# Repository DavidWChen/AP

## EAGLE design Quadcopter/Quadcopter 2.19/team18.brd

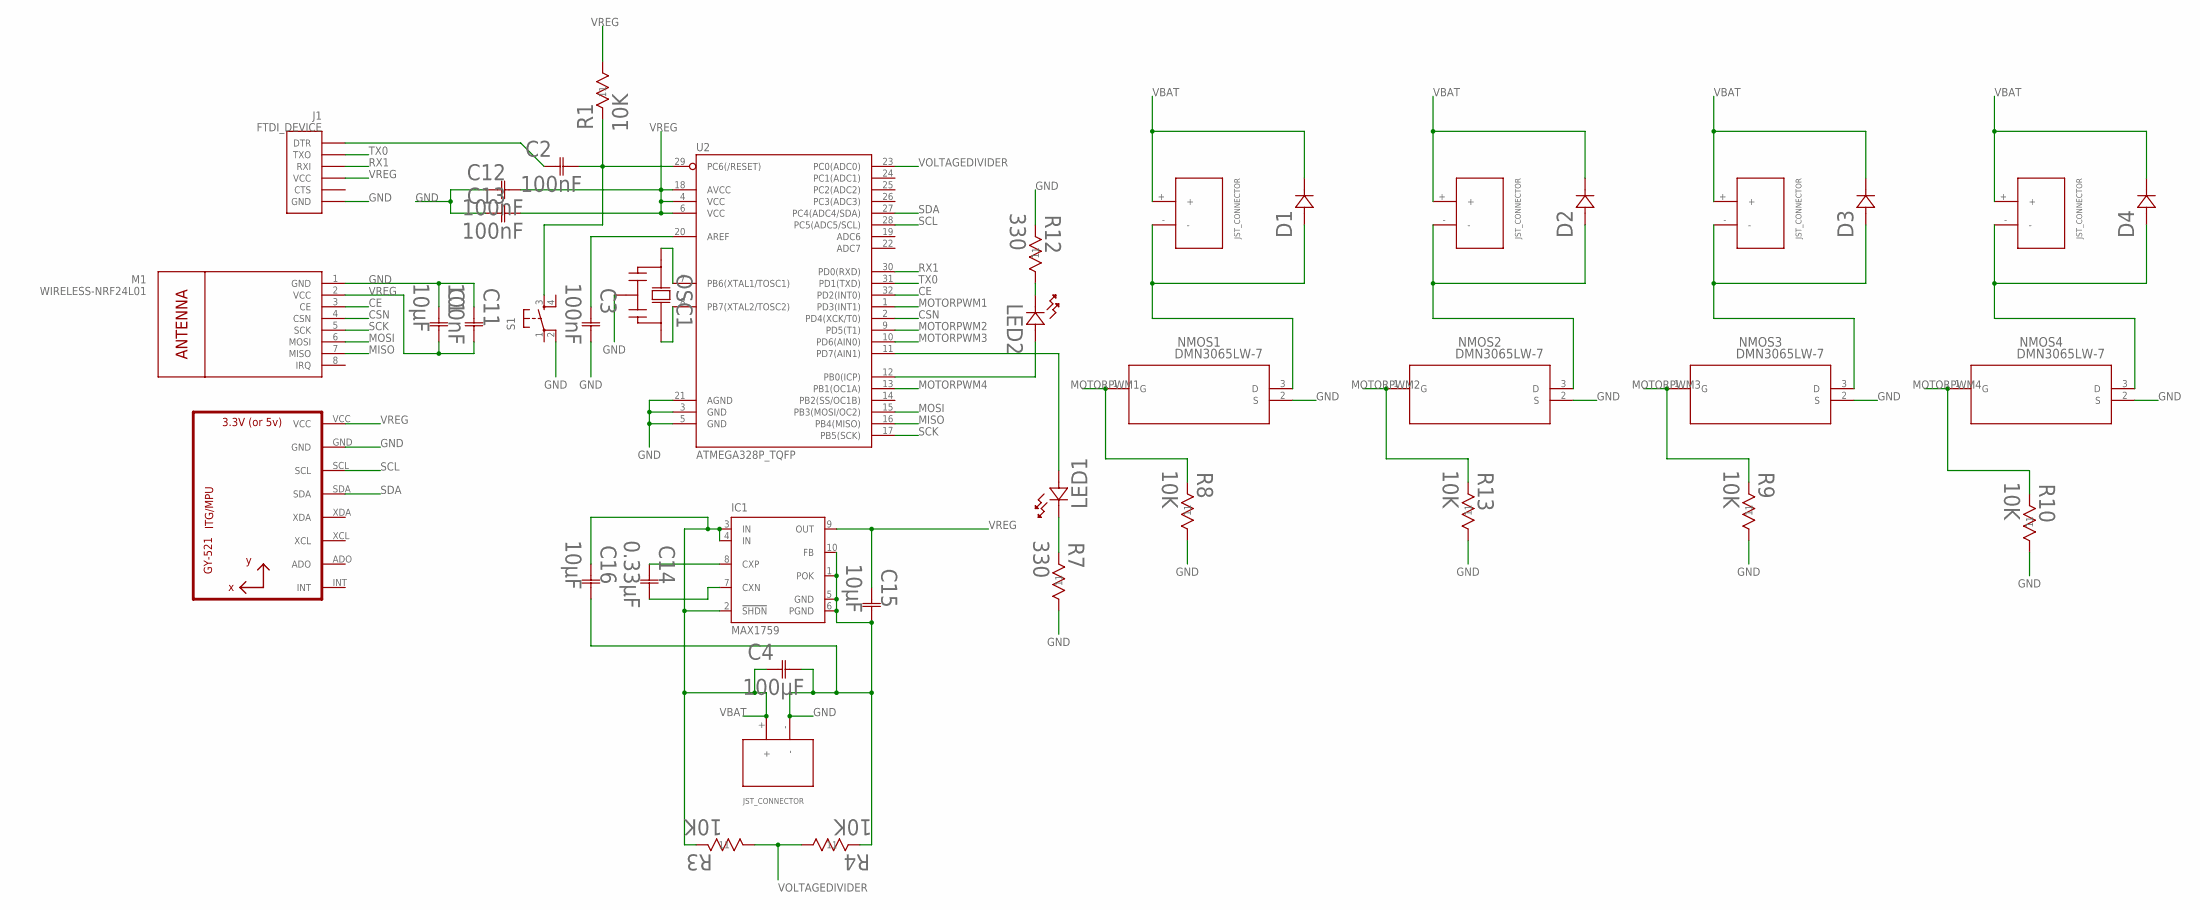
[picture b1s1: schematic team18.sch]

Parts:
BATTERY: JST_CONNECTOR_FEMALE
C1, C15, C16: 10µF; G-188
C2, C3, C11, C12, C13: 100nF; CAP_1608
C4: 100µF; CAP_3216
C14: 0.33µF; G-188
D1, D2, D3, D4: BAT60JFILM; SOD-323
IC1: MAX1759; UMAX10
J1: FTDI_DEVICE; FTDI_DEVICE_SIDE
LED1, LED2: 5988070107F; LED_DIALIGHT_598
M1: WIRELESS-NRF24L01
MOTOR1, MOTOR2, MOTOR3, MOTOR4: JST_CONNECTOR_FEMALE
NMOS1, NMOS2, NMOS3, NMOS4: DMN3065LW-7; SOT-323W/NEW
OSC1: CSTCE8M00G52-R0; CSTCE
R1, R3, R4, R8, R9, R10, R13: 10K; 0603
R7, R12: 330; BO_CR0603
S1: TAC_SWITCHSMD; TACTILE_SWITCH_SMD
U1: GY-521MPU6050; GY-521
U2: ATMEGA328P_TQFP; TQFP32-08

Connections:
CE: M1.3 (CE), U2.32 (PD2(INT0))
CSN: M1.4 (CSN), U2.2 (PD4(XCK/T0))
GND: BATTERY.-, C1.1 (11), C3.2 (22), C4.2 (22), C11.1 (11), C12.1 (11), C13.1 (11), C15.2 (22), C16.2 (22), IC1.1 (POK), IC1.5 (GND), IC1.6 (PGND), IC1.10 (FB), J1.P$6 (GND), M1.1 (GND), NMOS1.2 (S), NMOS2.2 (S), NMOS3.2 (S), NMOS4.2 (S), OSC1.2 (22), R4.1 (11), R7.2 (22), R8.2 (22), R9.2 (22), R10.2 (22), R12.1 (11), R13.2 (22), S1.2, U1.GND, U2.3 (GND), U2.5 (GND), U2.21 (AGND)
MISO: M1.7 (MISO), U2.16 (PB4(MISO))
MOSI: M1.6 (MOSI), U2.15 (PB3(MOSI/OC2))
MOTORPWM1: NMOS1.1 (G), R8.1 (11), U2.1 (PD3(INT1))
MOTORPWM2: NMOS2.1 (G), R13.1 (11), U2.9 (PD5(T1))
MOTORPWM3: NMOS3.1 (G), R9.1 (11), U2.10 (PD6(AIN0))
MOTORPWM4: NMOS4.1 (G), R10.1 (11), U2.13 (PB1(OC1A))
unnamed: D2.2 (22), MOTOR2.-, NMOS2.3 (D)
unnamed: C14.1 (11), IC1.8 (CXP)
unnamed: D3.2 (22), MOTOR3.-, NMOS3.3 (D)
unnamed: D4.2 (22), MOTOR4.-, NMOS4.3 (D)
unnamed: C2.2 (22), R1.1 (11), S1.3, U2.29 (PC6(/RESET))
unnamed: D1.2 (22), MOTOR1.-, NMOS1.3 (D)
unnamed: C2.1 (11), J1.P$1 (DTR)
unnamed: C14.2 (22), IC1.7 (CXN)
unnamed: LED1.2 (22), U2.11 (PD7(AIN1))
unnamed: LED2.2 (22), U2.12 (PB0(ICP))
unnamed: C3.1 (11), U2.20 (AREF)
unnamed: LED1.1 (11), R7.1 (11)
unnamed: OSC1.3 (33), U2.7 (PB6(XTAL1/TOSC1))
unnamed: OSC1.1 (11), U2.8 (PB7(XTAL2/TOSC2))
unnamed: LED2.1 (11), R12.2 (22)
RX1: J1.P$3 (RXI), U2.30 (PD0(RXD))
SCK: M1.5 (SCK), U2.17 (PB5(SCK))
SCL: U1.SCL, U2.28 (PC5(ADC5/SCL))
SDA: U1.SDA, U2.27 (PC4(ADC4/SDA))
TX0: J1.P$2 (TXO), U2.31 (PD1(TXD))
VBAT: BATTERY.+, C4.1 (11), C16.1 (11), D1.1 (11), D2.1 (11), D3.1 (11), D4.1 (11), IC1.2 (!SHDN), IC1.3 (IN), IC1.4 (IN), MOTOR1.+, MOTOR2.+, MOTOR3.+, MOTOR4.+, R3.1 (11)
VOLTAGEDIVIDER: R3.2 (22), R4.2 (22), U2.23 (PC0(ADC0))
VREG: C1.2 (22), C11.2 (22), C12.2 (22), C13.2 (22), C15.1 (11), IC1.9 (OUT), J1.P$4 (VCC), M1.2 (VCC), R1.2 (22), U1.VCC, U2.4 (VCC), U2.6 (VCC), U2.18 (AVCC)

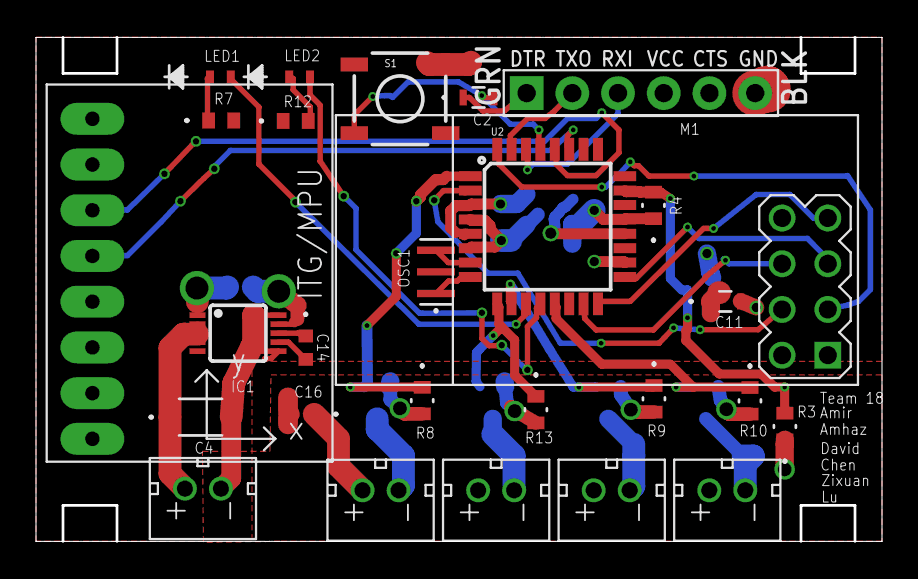
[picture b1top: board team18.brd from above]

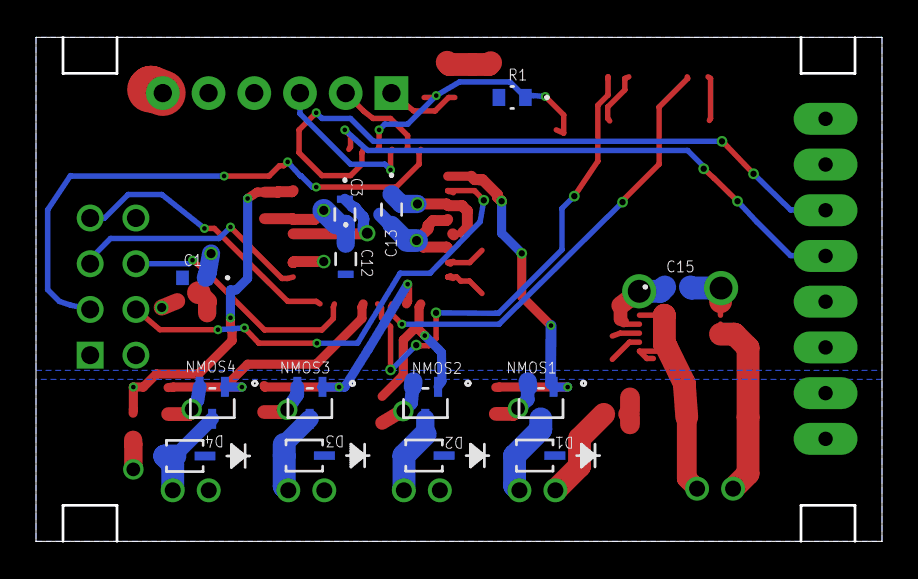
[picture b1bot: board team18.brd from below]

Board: 2 copper layers, 46.8 x 28.0 mm, 41 parts (14 on the bottom side), 32 nets.

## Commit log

2019-04-07 quadcopter

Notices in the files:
parts and their libraries:
SparkFun: Licensing: CC v3.0 Share-Alike You are welcome to use this library for commercial purposes.
